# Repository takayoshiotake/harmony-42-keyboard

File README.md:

# Harmony 42

[![CC BY-SA 4.0][cc-by-sa-shield]][cc-by-sa]
[![FreeCAD][freecad-shield]][freecad]
[![Inkscape][inkscape-shield]][inkscape]
[![KiCad][kicad-shield]][kicad]
[![Vial][vial-shield]][vial]

A 42-key keyboard.

- Switch: TTC Frozen V2
- Keycap: StarryPoem + HIBI Artisan

## Concept

## Layout

v0.1.0

- width: 14u
- depth: <6u

Made with Python script: 📁 [editor](layout/editor)

- 📄 [locations.csv](layout/locations.csv)
- 📄 [keyboard-layout.rawdata.json](layout/keyboard-layout.rawdata.json)

## BOM

| Material | QTY | Note |
|-|-:|-|
| Harmony 42 PCB | 1 | [Schematic-and-PCB](#schematic-and-pcb) |
| MCU 16 PCB | 1 | [Schematic-and-PCB](#schematic-and-pcb) |
| Harmony 42 Case | 1 | PMMA CNC, [Mechanics](#mechanics) |
| Harmony 42 Gasket | 1 | PORON 2mm, [Mechanics](#mechanics) |
| Harmony 42 Plate | 1 | Acrylic 1.5mm, [Mechanics](#mechanics) |
| FFC | 1 | 16 ciruits, 0.50mm pitch, Type D (opposite sides), >50mm length |
| Screw: M2 x 4mm | 5 | |

## Schematic and PCB

KiCad files:

- 📄 [harmony-42-pcb.kicad_sch](electronics/harmony-42-pcb/harmony-42-pcb.kicad_sch) (v1.0.0)
- 📄 [harmony-42-pcb.kicad_pcb](electronics/harmony-42-pcb/harmony-42-pcb.kicad_pcb) (v1.0.0)
- 📄 [mcu-16-pcb.kicad_sch](electronics/mcu-16-pcb/mcu-16-pcb.kicad_sch) (v1.0.0)
- 📄 [mcu-16-pcb.kicad_pcb](electronics/mcu-16-pcb/mcu-16-pcb.kicad_pcb) (v1.0.0)

## Mechanics

Files:

- 📄 [harmony-42-case-topview.svg](mechanics/harmony-42-case-topview.svg)
    - 📄 [1.5mm PMMA plate for 遊舎工房 レーザー加工サービス](mechanics/harmony-42-plate_Laser_A4_template_inkscape.svg)
        - アクリル クリア 1.5mm A4
    - 📄 [2mm PORON gasket for 遊舎工房 レーザー加工サービス](mechanics/harmony-42-gasket_Poron%20laserCut%20Template%202022-10-20_OUTLINED.svg)
        - フォーム 2mm 297x190接着シート付き
- 📄 [harmony-42-case.FCStd](mechanics/harmony-42-case.FCStd)
    - 📄 [harmony-42-case-Top.step](mechanics/harmony-42-case-Top.step)
    - 📄 [harmony-42-case-Bottom.step](mechanics/harmony-42-case-Bottom.step)

## Firmware

### Vial

- Built UF2
    - 📄 [takayoshiotake_harmony_42_vial_20240726.uf2](vial-bin/takayoshiotake_harmony_42_vial_20240726.uf2)
- Code
    - 🔗 <https://github.com/vial-kb/vial-qmk/tree/vial/keyboards/takayoshiotake/harmony_42>

See [vial-porting](vial-porting) for more details.

## License

This work is licensed under a
[Creative Commons Attribution-ShareAlike 4.0 International License][cc-by-sa].

[![CC BY-SA 4.0][cc-by-sa-image]][cc-by-sa]

[cc-by-sa]: http://creativecommons.org/licenses/by-sa/4.0/
[cc-by-sa-image]: https://licensebuttons.net/l/by-sa/4.0/88x31.png
[cc-by-sa-shield]: https://img.shields.io/badge/license-CC%20BY--SA%204.0-lightgrey.svg

[freecad]: https://www.freecad.org/
[freecad-shield]: https://img.shields.io/badge/FreeCAD-gray.svg?logo=freecad

[inkscape]: https://inkscape.org/
[inkscape-shield]: https://img.shields.io/badge/Inkscape-gray.svg?logo=inkscape&logoColor=000000

[kicad]: https://www.kicad.org/
[kicad-shield]: https://img.shields.io/badge/KiCad-314CB0.svg

[vial]: https://get.vial.today/
[vial-shield]: https://img.shields.io/badge/Vial-03045E.svg

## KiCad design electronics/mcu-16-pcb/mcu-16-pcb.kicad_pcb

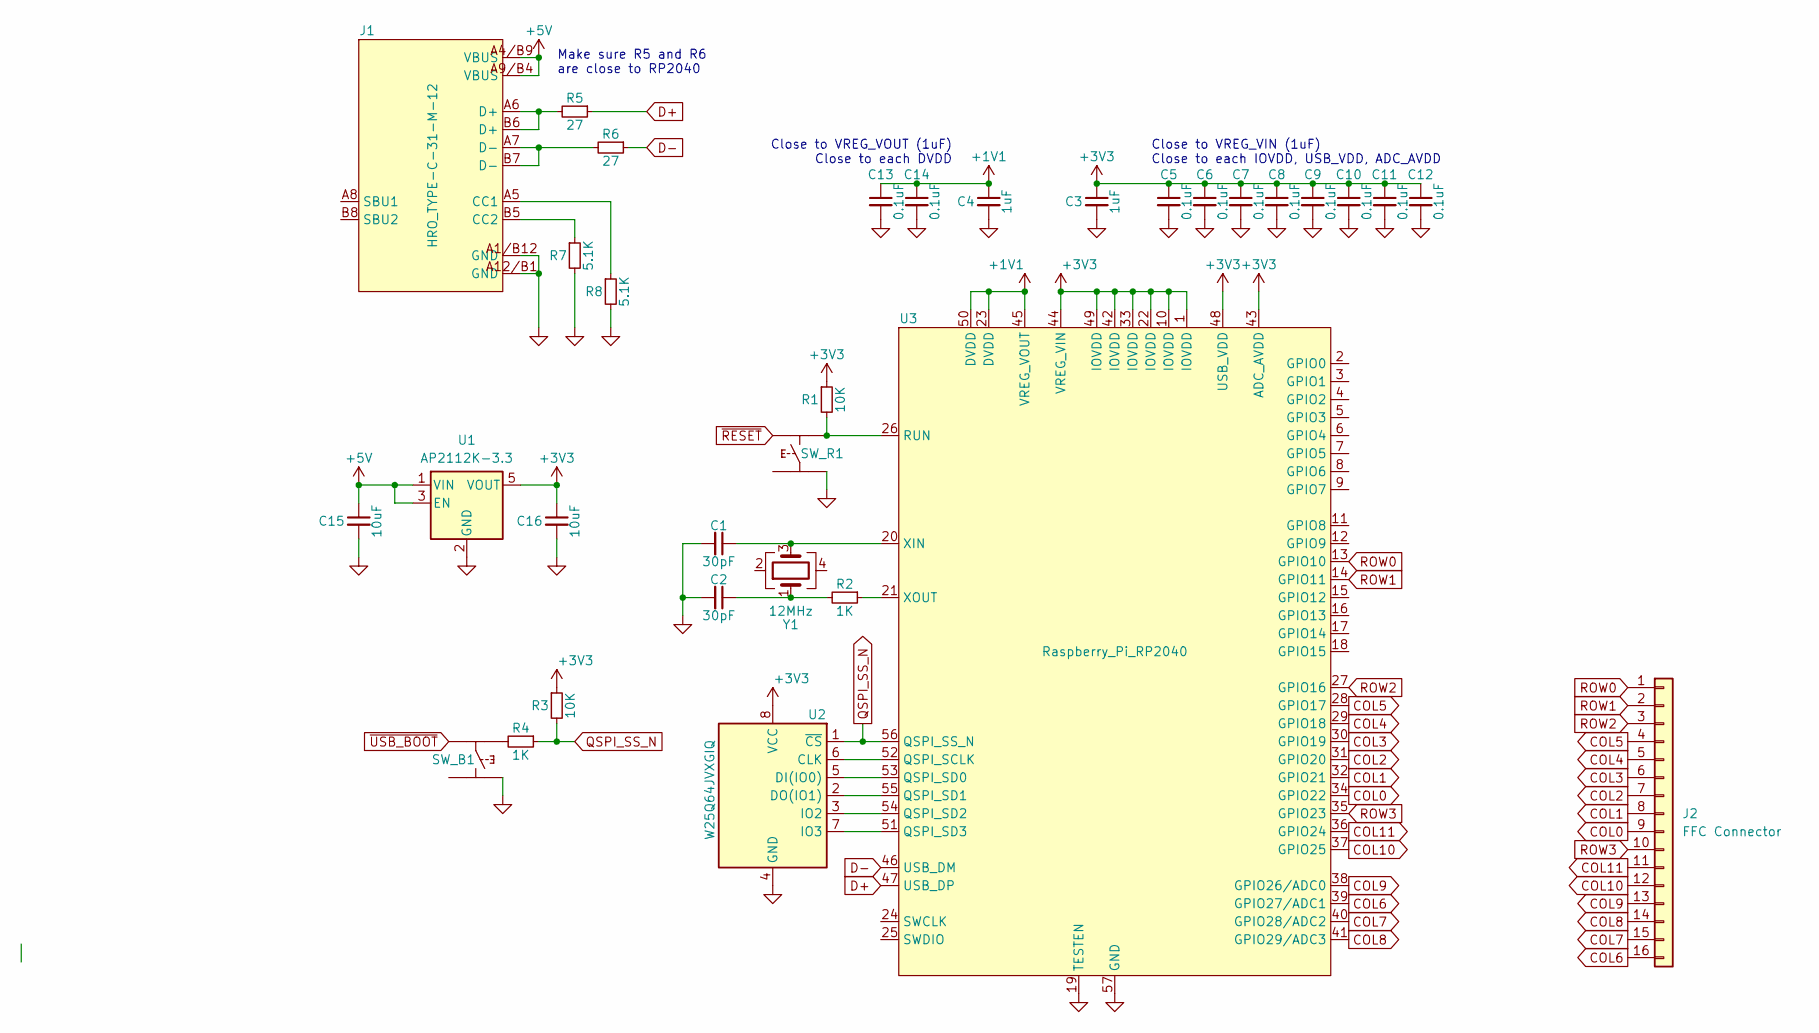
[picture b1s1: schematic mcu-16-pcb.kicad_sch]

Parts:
C1, C2: 30pF; C_0402_1005Metric; LCSC C1570
C3, C4: 1uF; C_0402_1005Metric; LCSC C52923
C5, C6, C7, C8, C9, C10, C11, C12, C13, C14: 0.1uF; C_0402_1005Metric; LCSC C307331
C15, C16: 10uF; C_0402_1005Metric; LCSC C15525
J1: HRO_TYPE-C-31-M-12; LCSC C165948
J2: FFC Connector; JUSHUO_AFC01-S16FCC-00; LCSC C262272
R1, R3: 10K; R_0402_1005Metric; LCSC C25744
R2, R4: 1K; R_0402_1005Metric; LCSC C11702
R5, R6: 27; R_0402_1005Metric; LCSC C25100
R7, R8: 5.1K; R_0402_1005Metric; LCSC C25905
SW_B1: Alps_Alpine_SKRP; Tactile_Switch_SKRP_Series; LCSC C115360
SW_R1: Alps_Alpine_SKRP; Tactile_Switch_SKRP_Series; LCSC C115360
U1: AP2112K-3.3; SOT-23-5; LCSC C51118
U2: W25Q64JVXGIQ; XSON-8-EP_4x4mm; LCSC C2940195
U3: Raspberry_Pi_RP2040; RP2040_QFN-56; LCSC C2040
Y1: 12MHz; Crystal_SMD_3225-4Pin_3.2x2.5mm; LCSC C9002

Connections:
+1V1: C4.1, C13.1, C14.1, U3.23 (DVDD), U3.45 (VREG_VOUT), U3.50 (DVDD)
+3V3: C3.1, C5.1, C6.1, C7.1, C8.1, C9.1, C10.1, C11.1, C12.1, C16.1, R1.1, R3.1, U1.5 (VOUT), U2.8 (VCC), U3.1 (IOVDD), U3.10 (IOVDD), U3.22 (IOVDD), U3.33 (IOVDD), U3.42 (IOVDD), U3.43 (ADC_AVDD), U3.44 (VREG_VIN), U3.48 (USB_VDD), U3.49 (IOVDD)
+5V: C15.1, J1.A4/B9 (VBUS), J1.A9/B4 (VBUS), U1.1 (VIN), U1.3 (EN)
COL0: J2.9, U3.34 (GPIO22)
COL1: J2.8, U3.32 (GPIO21)
COL2: J2.7, U3.31 (GPIO20)
COL3: J2.6, U3.30 (GPIO19)
COL4: J2.5, U3.29 (GPIO18)
COL5: J2.4, U3.28 (GPIO17)
COL6: J2.16, U3.39 (GPIO27/ADC1)
COL7: J2.15, U3.40 (GPIO28/ADC2)
COL8: J2.14, U3.41 (GPIO29/ADC3)
COL9: J2.13, U3.38 (GPIO26/ADC0)
COL10: J2.12, U3.37 (GPIO25)
COL11: J2.11, U3.36 (GPIO24)
D+: R5.1, U3.47 (USB_DP)
D-: R6.1, U3.46 (USB_DM)
GND: C1.2, C2.2, C3.2, C4.2, C5.2, C6.2, C7.2, C8.2, C9.2, C10.2, C11.2, C12.2, C13.2, C14.2, C15.2, C16.2, J1.A1/B12 (GND), J1.A12/B1 (GND), R7.2, R8.2, SW_B1.4, SW_R1.1, U1.2 (GND), U2.4 (GND), U3.19 (TESTEN), U3.57 (GND)
unnamed: C2.1, R2.2, Y1.1
unnamed: J1.A5 (CC1), R8.1
unnamed: J1.B5 (CC2), R7.1
unnamed: J1.A6 (D+), J1.B6 (D+), R5.2
unnamed: J1.A7 (D-), J1.B7 (D-), R6.2
unnamed: R4.2, SW_B1.2
unnamed: U2.6 (CLK), U3.52 (QSPI_SCLK)
unnamed: U2.5 (DI(IO0)), U3.53 (QSPI_SD0)
unnamed: U2.2 (DO(IO1)), U3.55 (QSPI_SD1)
unnamed: U2.3 (IO2), U3.54 (QSPI_SD2)
unnamed: U2.7 (IO3), U3.51 (QSPI_SD3)
unnamed: R1.2, SW_R1.3, U3.26 (RUN)
unnamed: C1.1, U3.20 (XIN), Y1.3
unnamed: R2.1, U3.21 (XOUT)
QSPI_SS_N: R3.2, R4.1, U2.1 (~CS), U3.56 (QSPI_SS_N)
ROW0: J2.1, U3.13 (GPIO10)
ROW1: J2.2, U3.14 (GPIO11)
ROW2: J2.3, U3.27 (GPIO16)
ROW3: J2.10, U3.35 (GPIO23)
~RESET: SW_R1.4
~USB_BOOT: SW_B1.1

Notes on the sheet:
Close to VREG_VIN (1uF) Close to each IOVDD, USB_VDD, ADC_AVDD
Close to VREG_VOUT (1uF) Close to each DVDD
Make sure R5 and R6 are close to RP2040

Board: 2 copper layers, 32 parts (0 on the bottom side), 37 nets, no tracks yet.

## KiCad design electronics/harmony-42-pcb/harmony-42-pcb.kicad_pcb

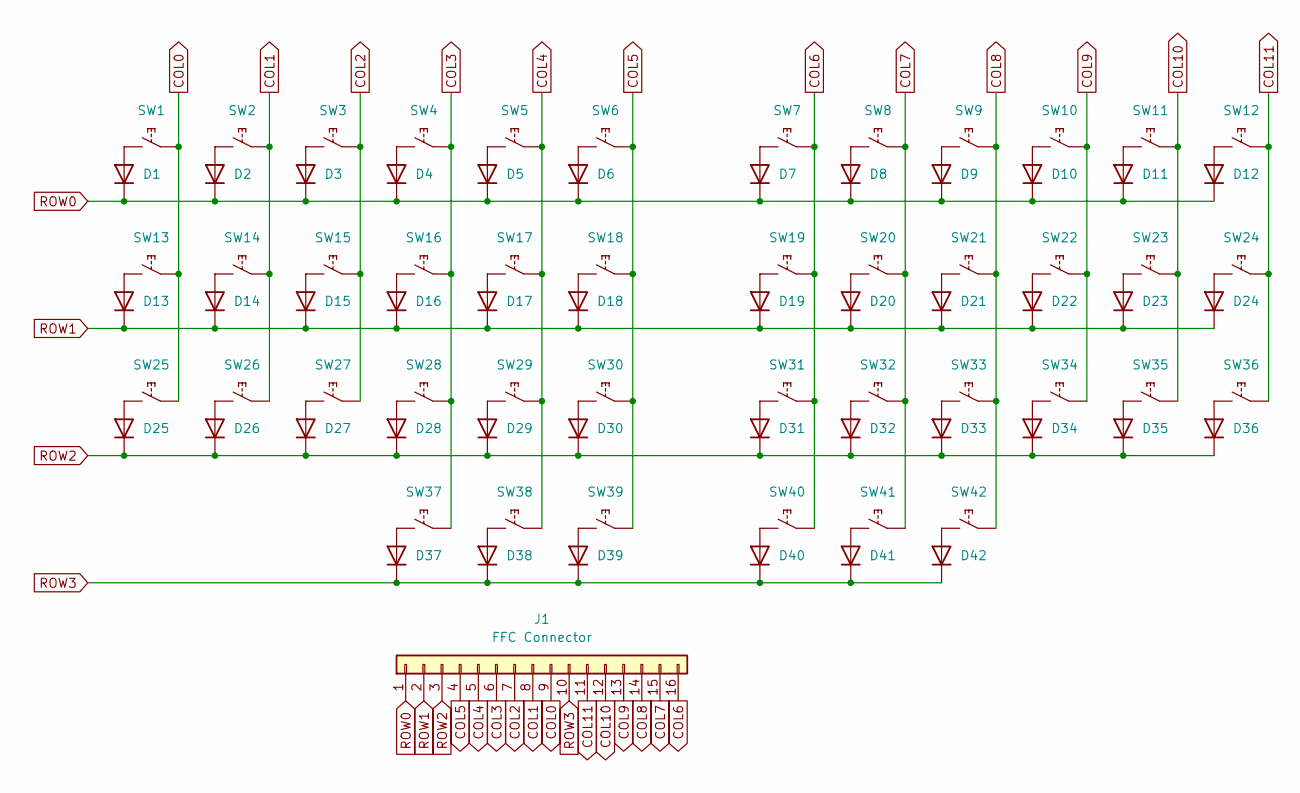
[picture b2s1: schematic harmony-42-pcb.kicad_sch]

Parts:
D1, D2, D3, D4, D5, D6, D7, D8, D9, D10, D11, D12, D13, D14, D15, D16, D17, D18, D19, D20, D21, D22, D23, D24, D25, D26, D27, D28, D29, D30, D31, D32, D33, D34, D35, D36, D37, D38, D39, D40, D41, D42: 1N4148WS; D_SOD-323F; LCSC C2128
J1: FFC Connector; JUSHUO_AFC01-S16FCC-00; LCSC C262272
SW1, SW2, SW3, SW4, SW5, SW6, SW7, SW8, SW9, SW10, SW11, SW12, SW13, SW14, SW15, SW16, SW17, SW18, SW19, SW20, SW21, SW22, SW23, SW24, SW25, SW26, SW27, SW28, SW29, SW30, SW31, SW32, SW33, SW34, SW35, SW36, SW37, SW38, SW39, SW40, SW41, SW42: Hot_Swap_Socket_CPG151101S11; LCSC C5156480

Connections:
COL0: J1.9, SW1.1, SW13.1, SW25.1
COL1: J1.8, SW2.1, SW14.1, SW26.1
COL2: J1.7, SW3.1, SW15.1, SW27.1
COL3: J1.6, SW4.1, SW16.1, SW28.1, SW37.1
COL4: J1.5, SW5.1, SW17.1, SW29.1, SW38.1
COL5: J1.4, SW6.1, SW18.1, SW30.1, SW39.1
COL6: J1.16, SW7.1, SW19.1, SW31.1, SW40.1
COL7: J1.15, SW8.1, SW20.1, SW32.1, SW41.1
COL8: J1.14, SW9.1, SW21.1, SW33.1, SW42.1
COL9: J1.13, SW10.1, SW22.1, SW34.1
COL10: J1.12, SW11.1, SW23.1, SW35.1
COL11: J1.11, SW12.1, SW24.1, SW36.1
unnamed: D1.2 (A), SW1.2
unnamed: D2.2 (A), SW2.2
unnamed: D3.2 (A), SW3.2
unnamed: D4.2 (A), SW4.2
unnamed: D5.2 (A), SW5.2
unnamed: D6.2 (A), SW6.2
unnamed: D7.2 (A), SW7.2
unnamed: D8.2 (A), SW8.2
unnamed: D9.2 (A), SW9.2
unnamed: D10.2 (A), SW10.2
unnamed: D11.2 (A), SW11.2
unnamed: D12.2 (A), SW12.2
unnamed: D13.2 (A), SW13.2
unnamed: D14.2 (A), SW14.2
unnamed: D15.2 (A), SW15.2
unnamed: D16.2 (A), SW16.2
unnamed: D17.2 (A), SW17.2
unnamed: D18.2 (A), SW18.2
unnamed: D19.2 (A), SW19.2
unnamed: D20.2 (A), SW20.2
unnamed: D21.2 (A), SW21.2
unnamed: D22.2 (A), SW22.2
unnamed: D23.2 (A), SW23.2
unnamed: D24.2 (A), SW24.2
unnamed: D25.2 (A), SW25.2
unnamed: D26.2 (A), SW26.2
unnamed: D27.2 (A), SW27.2
unnamed: D28.2 (A), SW28.2
unnamed: D29.2 (A), SW29.2
unnamed: D30.2 (A), SW30.2
unnamed: D31.2 (A), SW31.2
unnamed: D32.2 (A), SW32.2
unnamed: D33.2 (A), SW33.2
unnamed: D34.2 (A), SW34.2
unnamed: D35.2 (A), SW35.2
unnamed: D36.2 (A), SW36.2
unnamed: D37.2 (A), SW37.2
unnamed: D38.2 (A), SW38.2
unnamed: D39.2 (A), SW39.2
unnamed: D40.2 (A), SW40.2
unnamed: D41.2 (A), SW41.2
unnamed: D42.2 (A), SW42.2
ROW0: D1.1 (K), D2.1 (K), D3.1 (K), D4.1 (K), D5.1 (K), D6.1 (K), D7.1 (K), D8.1 (K), D9.1 (K), D10.1 (K), D11.1 (K), D12.1 (K), J1.1
ROW1: D13.1 (K), D14.1 (K), D15.1 (K), D16.1 (K), D17.1 (K), D18.1 (K), D19.1 (K), D20.1 (K), D21.1 (K), D22.1 (K), D23.1 (K), D24.1 (K), J1.2
ROW2: D25.1 (K), D26.1 (K), D27.1 (K), D28.1 (K), D29.1 (K), D30.1 (K), D31.1 (K), D32.1 (K), D33.1 (K), D34.1 (K), D35.1 (K), D36.1 (K), J1.3
ROW3: D37.1 (K), D38.1 (K), D39.1 (K), D40.1 (K), D41.1 (K), D42.1 (K), J1.10

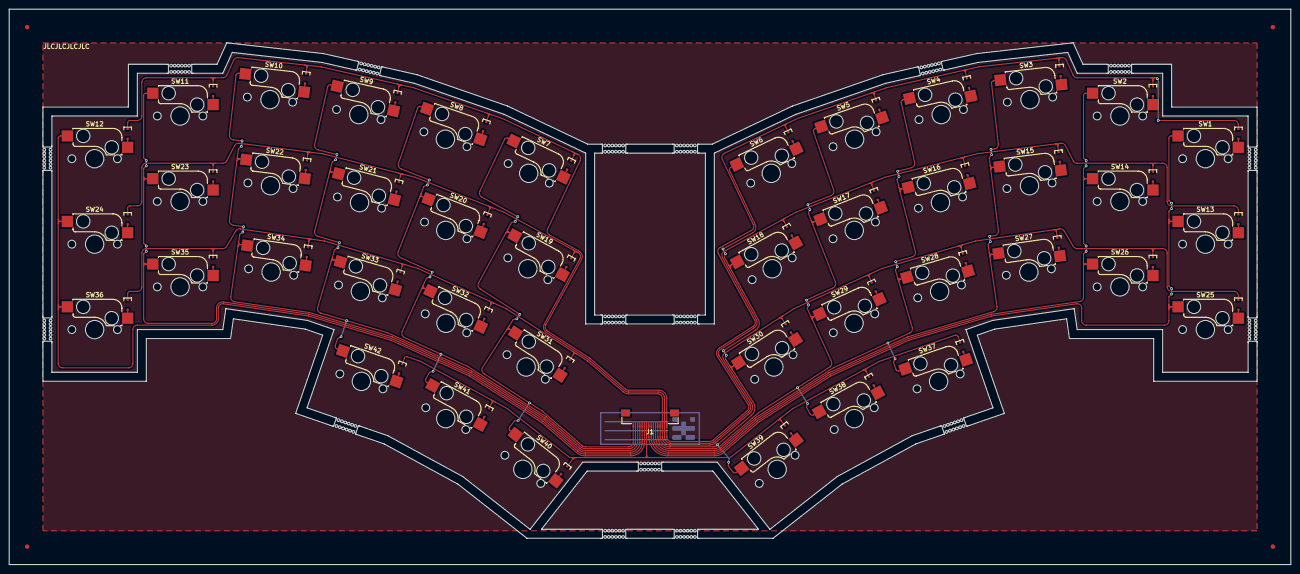
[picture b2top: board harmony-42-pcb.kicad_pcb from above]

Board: 2 copper layers, 285.7 x 123.8 mm, 85 parts (0 on the bottom side), 58 nets.

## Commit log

2024-06-16 Init
2024-06-16 Add concept image
2024-06-16 Remove img style
2024-06-17 Add layout image
    The layout is made with Python scripts in the layout/editor.
2024-06-18 Add kicad project for PCB
2024-06-18 Add keys
2024-06-18 Add diodes
2024-06-19 Fix mounting side of parts
2024-06-22 Move diodes
2024-06-22 Route some sw
2024-06-23 Add routes
2024-06-24 Add routes for one side
2024-06-24 Fix fillet radius
2024-07-02 Change routes
2024-07-05 Update pcb
2024-07-07 Add production data
2024-07-07 Add PCB images
2024-07-07 Move files
2024-07-09 Add simple version PCB design
2024-07-14 Add vial porting codes and built uf2
2024-07-14 Change uid in vial
2024-07-14 Add mcu kicad project
2024-07-15 WIP Update
2024-07-15 Update MCU 16 pcb
2024-07-18 Add MCU 16 files
2024-07-18 Add kicad project for plate
2024-07-18 Add key locations data on PCB
2024-07-21 Update case design
2024-07-21 Update MCU 16 position
2024-07-21 Update case gap for poron
2024-07-21 Rename
2024-07-21 Change poron to gasket
2024-07-21 Update gasket: poron 2mm
2024-07-22 Make 3d data
2024-07-23 Add plate 3d data
2024-07-26 Update vial fw for MCU 16
2024-07-26 Add MCU 16 info
2024-07-26 Update 2d top-view with fillet
2024-07-26 Update plate design
2024-07-27 Add gasket cutting design
2024-08-16 Add case image
2024-08-18 Add keyboard photo
2024-08-22 Add link to vial code
2024-09-01 Add BOM table
